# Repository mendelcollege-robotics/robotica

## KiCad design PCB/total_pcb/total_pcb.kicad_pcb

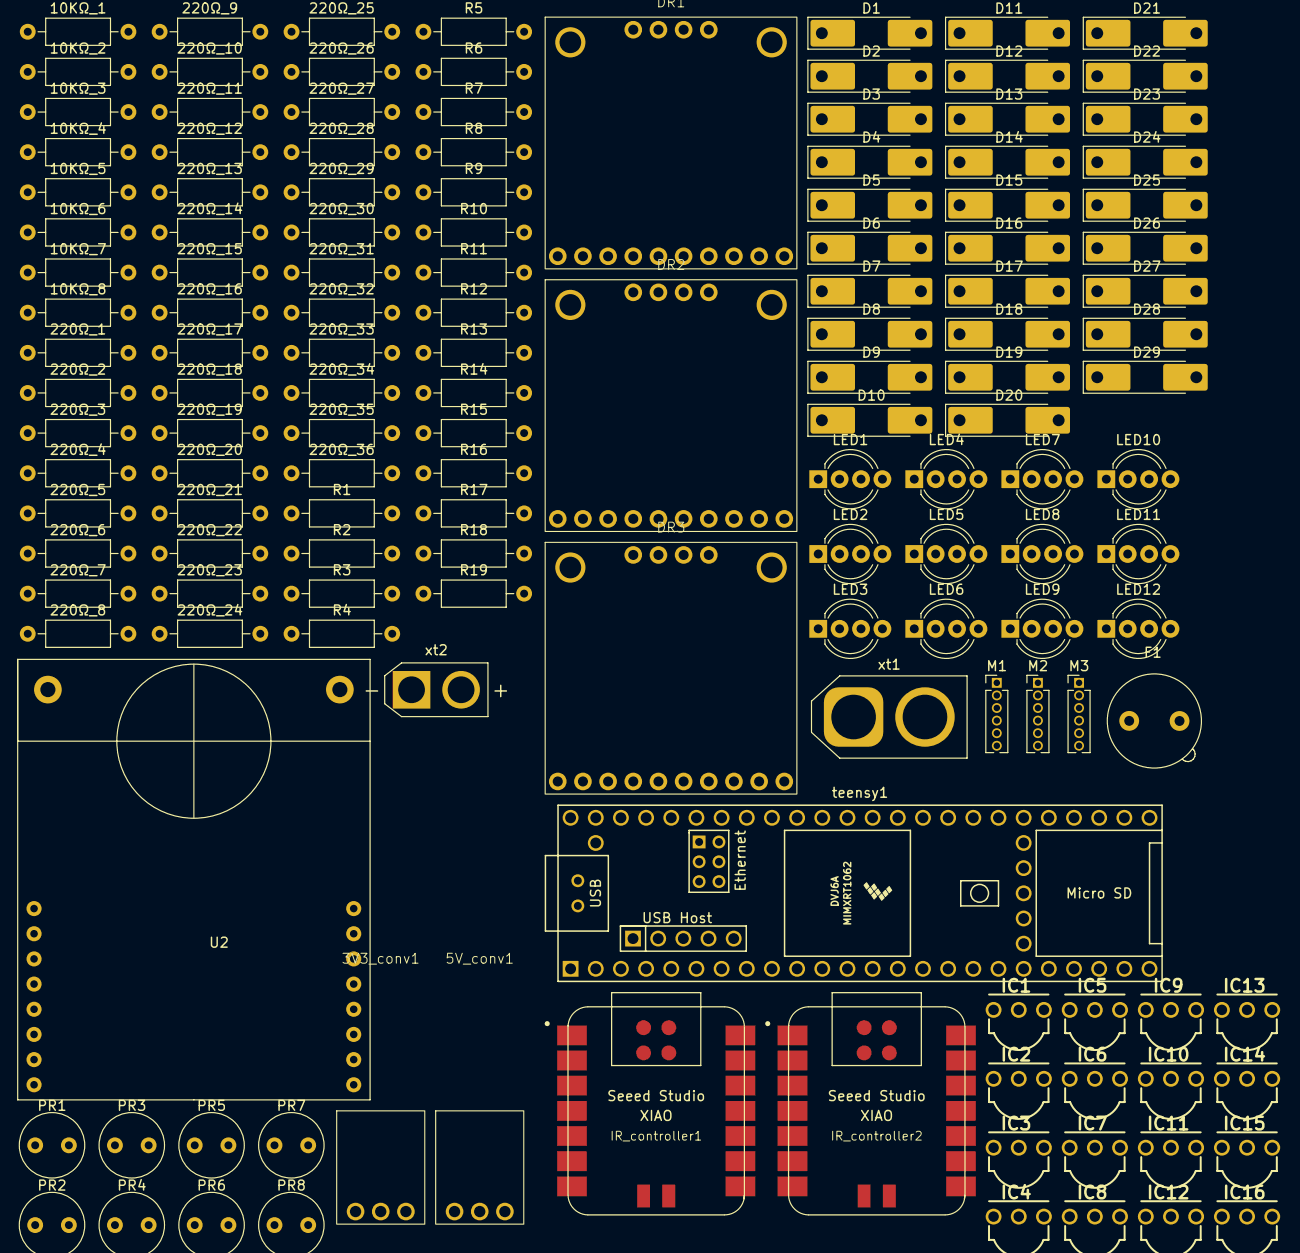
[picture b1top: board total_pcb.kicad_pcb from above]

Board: 2 copper layers, 143 parts (0 on the bottom side), 140 nets, no tracks yet.

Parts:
3V3_conv1, 5V_conv1: pololu-U1V10F5
10KΩ_1, 10KΩ_2, 10KΩ_3, 10KΩ_4, 10KΩ_5, 10KΩ_6, 10KΩ_7, 10KΩ_8, 220Ω_1, 220Ω_2, 220Ω_3, 220Ω_4, 220Ω_5, 220Ω_6, 220Ω_7, 220Ω_8, 220Ω_9, 220Ω_10, 220Ω_11, 220Ω_12, 220Ω_13, 220Ω_14, 220Ω_15, 220Ω_16, 220Ω_17, 220Ω_18, 220Ω_19, 220Ω_20, 220Ω_21, 220Ω_22, 220Ω_23, 220Ω_24, 220Ω_25, 220Ω_26, 220Ω_27, 220Ω_28, 220Ω_29, 220Ω_30, 220Ω_31, 220Ω_32, 220Ω_33, 220Ω_34, 220Ω_35, 220Ω_36: R_US; R_Axial_DIN0207_L6.3mm_D2.5mm_P10.16mm_Horizontal
D1, D2, D3, D4, D5, D6, D7, D8, D9, D10, D11, D12, D13, D14, D15, D16, D17, D18, D19, D20, D21, D22, D23, D24, D25, D26, D27, D28, D29: D; D_MELF-RM10_Universal_Handsoldering
DR1, DR2, DR3: TB9051FTG
F1: Fuse; Fuseholder_TR5_Littelfuse_No560_No460
IC1, IC2, IC3, IC4, IC5, IC6, IC7, IC8, IC9, IC10, IC11, IC12, IC13, IC14, IC15, IC16: TSSP4038
IR_controller1, IR_controller2: Seeed Studio XIAO SAMD21; XIAO-SAMD21-RP2040-14P-2.54-21X17.8MM (Seeeduino XIAO)
LED1, LED2, LED3, LED4, LED5, LED6, LED7, LED8, LED9, LED10, LED11, LED12: LED_KRGB; LED_D5.0mm-4_RGB_Wide_Pins
M1, M2, M3: PinHeader_1x06_P1.27mm_Vertical
PR1, PR2, PR3, PR4, PR5, PR6, PR7, PR8: A1050; R_LDR_D6.4mm_P3.4mm_Vertical
R1, R2, R3, R4, R5, R6, R7, R8, R9, R10, R11, R12, R13, R14, R15, R16, R17, R18, R19: R_US; R_Axial_DIN0207_L6.3mm_D2.5mm_P10.16mm_Horizontal
U2: openMV_M7_R2; openmv_m7_r2
teensy1: Teensy4.1; Teensy41
xt1: Battery; AMASS_XT60-F_1x02_P7.20mm_Vertical
xt2: Battery; AMASS_XT30U-M_1x02_P5.0mm_Vertical

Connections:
3v3: D7.2 (A), D21.1 (K)
5V: D16.2 (A), D23.1 (K)
5v: D8.2 (A), D20.1 (K)
BLAUW: R17.2, teensy1.38 (16_A2_RX4_SCL1)
GND: D17.1 (K), D24.2 (A), D26.2 (A)
GROEN: R18.2, teensy1.25 (33_MCLK2)
unnamed: 3V3_conv1.3 (VIN), 5V_conv1.3 (VIN), D12.1 (K)
unnamed: D1.2 (A), D4.2 (A), D7.1 (K)
unnamed: D1.1 (K), IR_controller1.12 (3V3)
unnamed: D2.2 (A), IR_controller1.13 (GND)
unnamed: D2.1 (K), D3.1 (K), D5.1 (K), D9.2 (A), D29.1 (K), U2.screw
unnamed: D3.2 (A), IR_controller2.13 (GND)
unnamed: D4.1 (K), IR_controller2.12 (3V3)
unnamed: D5.2 (A), U2.17 (gnd)
unnamed: D6.1 (K), U2.16 (vin)
unnamed: D10.2 (A), xt1.2 (-), xt2.2 (-)
unnamed: D10.1 (K), F1.2
unnamed: D11.2 (A), D13.1 (K), D26.1 (K), D27.2 (A), DR1.0 (screw), DR1.6 (GND), DR2.0 (screw), DR2.6 (GND), DR3.0 (screw), DR3.6 (GND)
unnamed: D11.1 (K), xt1.1 (+), xt2.1 (+)
unnamed: D12.2 (A), D25.2 (A), DR1.1 (VIN), DR2.1 (VIN), DR3.1 (VIN), F1.1
unnamed: D13.2 (A), D19.1 (K), D22.1 (K), D24.1 (K)
unnamed: D14.1 (K), D18.2 (A), D20.2 (A), D23.2 (A), DR1.7 (VCC), DR2.7 (VCC), DR3.7 (VCC), M1.4 (Vcc), M2.4 (Vcc), M3.4 (Vcc)
unnamed: D15.1 (K), D21.2 (A)
unnamed: D16.1 (K), PR1.1, PR2.1, PR3.1, PR4.1, PR5.1, PR6.1, PR7.1, PR8.1
unnamed: 10KΩ_1.2, 10KΩ_2.2, 10KΩ_3.2, 10KΩ_4.2, 10KΩ_5.2, 10KΩ_6.2, 10KΩ_7.2, 10KΩ_8.2, D17.2 (A), LED1.1 (K), LED2.1 (K), LED3.1 (K), LED4.1 (K), LED5.1 (K), LED6.1 (K), LED7.1 (K), LED8.1 (K), LED9.1 (K), LED10.1 (K), LED11.1 (K), LED12.1 (K)
unnamed: D18.1 (K), teensy1.48 (VIN)
unnamed: D19.2 (A), teensy1.47 (GND)
unnamed: D27.1 (K), DR1.2 (GND), DR2.2 (GND), DR3.2 (GND), M1.3 (GND), M2.3 (GND), M3.3 (GND)
unnamed: D6.2 (A), D8.1 (K), D28.2 (A)
unnamed: D28.1 (K), R1.2, R2.2, R3.2, R4.2, R5.2, R6.2, R7.2, R8.2, R9.2, R10.2, R11.2, R12.2, R13.2, R14.2, R15.2, R16.2
unnamed: D29.2 (A), IC1.2 (GND), IC2.2 (GND), IC3.2 (GND), IC4.2 (GND), IC5.2 (GND), IC6.2 (GND), IC7.2 (GND), IC8.2 (GND), IC9.2 (GND), IC10.2 (GND), IC11.2 (GND), IC12.2 (GND), IC13.2 (GND), IC14.2 (GND), IC15.2 (GND), IC16.2 (GND)
unnamed: DR1.9 (EN), teensy1.19 (27_A13_SCK1)
unnamed: DR1.10 (ENB), teensy1.18 (26_A12_MOSI1)
unnamed: DR1.4 (OUT1), M1.1 (MotorPW)
unnamed: DR1.3 (OUT2), M1.2 (MotorPW)
unnamed: DR1.12 (PWM1), teensy1.16 (24_A10_TX6_SCL2)
unnamed: DR1.11 (PWM2), teensy1.17 (25_A11_RX6_SDA2)
unnamed: DR2.9 (EN), teensy1.14 (12_MISO_MQSL)
unnamed: DR2.10 (ENB), teensy1.13 (11_MOSI_CTX1)
unnamed: DR2.4 (OUT1), M2.1 (MotorPW)
unnamed: DR2.3 (OUT2), M2.2 (MotorPW)
unnamed: DR2.12 (PWM1), teensy1.11 (9_OUT1C)
unnamed: DR2.11 (PWM2), teensy1.12 (10_CS_MQSR)
unnamed: DR3.9 (EN), teensy1.8 (6_OUT1D)
unnamed: DR3.10 (ENB), teensy1.7 (5_IN2)
unnamed: DR3.4 (OUT1), M3.1 (MotorPW)
unnamed: DR3.3 (OUT2), M3.2 (MotorPW)
unnamed: DR3.12 (PWM1), teensy1.5 (3_LRCLK2)
unnamed: DR3.11 (PWM2), teensy1.6 (4_BCLK2)
unnamed: IC1.1 (OUT), IR_controller1.1 (PA02_A0_D0)
unnamed: IC1.3 (VS), R1.1
unnamed: IC2.1 (OUT), IR_controller1.2 (PA4_A1_D1)
unnamed: IC2.3 (VS), R2.1
unnamed: IC3.3 (VS), R3.1
unnamed: IC4.1 (OUT), IR_controller1.3 (PA10_A2_D2)
unnamed: IC4.3 (VS), R4.1
unnamed: IC5.1 (OUT), IR_controller1.4 (PA11_A3_D3)
unnamed: IC5.3 (VS), R5.1
unnamed: IC6.1 (OUT), IR_controller1.5 (PA8_A4_D4_SDA)
unnamed: IC6.3 (VS), R6.1
unnamed: IC7.1 (OUT), IR_controller1.6 (PA9_A5_D5_SCL)
unnamed: IC7.3 (VS), R7.1
unnamed: IC8.1 (OUT), IR_controller1.9 (PA7_A8_D8_SCK)
unnamed: IC8.3 (VS), R8.1
unnamed: IC9.1 (OUT), IR_controller2.1 (PA02_A0_D0)
unnamed: IC9.3 (VS), R9.1
unnamed: IC10.1 (OUT), IR_controller2.2 (PA4_A1_D1)
unnamed: IC10.3 (VS), R10.1
unnamed: IC11.3 (VS), R11.1
unnamed: IC12.1 (OUT), IR_controller2.3 (PA10_A2_D2)
unnamed: IC12.3 (VS), R12.1
unnamed: IC13.1 (OUT), IR_controller2.4 (PA11_A3_D3)
unnamed: IC13.3 (VS), R13.1
unnamed: IC14.1 (OUT), IR_controller2.5 (PA8_A4_D4_SDA)
unnamed: IC14.3 (VS), R14.1
unnamed: IC15.1 (OUT), IR_controller2.6 (PA9_A5_D5_SCL)
unnamed: IC15.3 (VS), R15.1
unnamed: IC16.1 (OUT), IR_controller2.9 (PA7_A8_D8_SCK)
unnamed: IC16.3 (VS), R16.1
unnamed: 220Ω_3.1, LED1.4 (BA)
unnamed: 220Ω_2.1, LED1.3 (GA)
unnamed: 220Ω_1.1, LED1.2 (RA)
unnamed: 220Ω_6.1, LED2.4 (BA)
unnamed: 220Ω_5.1, LED2.3 (GA)
unnamed: 220Ω_4.1, LED2.2 (RA)
unnamed: 220Ω_9.1, LED3.4 (BA)
unnamed: 220Ω_8.1, LED3.3 (GA)
unnamed: 220Ω_7.1, LED3.2 (RA)
unnamed: 220Ω_12.1, LED4.4 (BA)
unnamed: 220Ω_11.1, LED4.3 (GA)
unnamed: 220Ω_10.1, LED4.2 (RA)
unnamed: 220Ω_15.1, LED5.4 (BA)
unnamed: 220Ω_14.1, LED5.3 (GA)
unnamed: 220Ω_13.1, LED5.2 (RA)
unnamed: 220Ω_18.1, LED6.4 (BA)
unnamed: 220Ω_17.1, LED6.3 (GA)
unnamed: 220Ω_16.1, LED6.2 (RA)
unnamed: 220Ω_21.1, LED7.4 (BA)
unnamed: 220Ω_20.1, LED7.3 (GA)
unnamed: 220Ω_19.1, LED7.2 (RA)
unnamed: 220Ω_24.1, LED8.4 (BA)
unnamed: 220Ω_23.1, LED8.3 (GA)
unnamed: 220Ω_22.1, LED8.2 (RA)
unnamed: 220Ω_27.1, LED9.4 (BA)
unnamed: 220Ω_26.1, LED9.3 (GA)
unnamed: 220Ω_25.1, LED9.2 (RA)
unnamed: 220Ω_30.1, LED10.4 (BA)
unnamed: 220Ω_29.1, LED10.3 (GA)
unnamed: 220Ω_28.1, LED10.2 (RA)
unnamed: 220Ω_33.1, LED11.4 (BA)
unnamed: 220Ω_32.1, LED11.3 (GA)
unnamed: 220Ω_31.1, LED11.2 (RA)
unnamed: 220Ω_36.1, LED12.4 (BA)
unnamed: 220Ω_35.1, LED12.3 (GA)
unnamed: 220Ω_34.1, LED12.2 (RA)
unnamed: M1.5 (A_out), teensy1.20 (28_RX7)
unnamed: M1.6 (B_out), teensy1.45 (23_A9_CRX1_MCLK1)
unnamed: M2.5 (A_out), teensy1.22 (30_CRX3)
unnamed: M2.6 (B_out), teensy1.21 (29_TX7)
unnamed: M3.5 (A_out), teensy1.24 (32_OUT1B)
unnamed: M3.6 (B_out), teensy1.23 (31_CTX3)
unnamed: 220Ω_3.2, 220Ω_6.2, 220Ω_9.2, 220Ω_12.2, 220Ω_15.2, 220Ω_18.2, 220Ω_21.2, 220Ω_24.2, 220Ω_27.2, 220Ω_30.2, 220Ω_33.2, 220Ω_36.2
unnamed: 220Ω_2.2, 220Ω_5.2, 220Ω_8.2, 220Ω_11.2, 220Ω_14.2, 220Ω_17.2, 220Ω_20.2, 220Ω_23.2, 220Ω_26.2, 220Ω_29.2, 220Ω_32.2, 220Ω_35.2
unnamed: 220Ω_1.2, 220Ω_4.2, 220Ω_7.2, 220Ω_10.2, 220Ω_13.2, 220Ω_16.2, 220Ω_19.2, 220Ω_22.2, 220Ω_25.2, 220Ω_28.2, 220Ω_31.2, 220Ω_34.2
ROOD: R19.2, teensy1.26 (34_RX8)
gnd: D9.1 (K), D22.2 (A)
pr1: 10KΩ_1.1, PR1.2, teensy1.35 (13_SCK_LED)
pr2: 10KΩ_2.1, PR2.2, teensy1.33 (41_A17)
pr3: 10KΩ_3.1, PR3.2, teensy1.32 (40_A16)
pr4: 10KΩ_4.1, PR4.2, teensy1.31 (39_MISO1_OUT1A)
pr5: 10KΩ_5.1, PR5.2, teensy1.30 (38_CS1_IN1)
pr6: 10KΩ_6.1, PR6.2, teensy1.29 (37_CS)
pr7: 10KΩ_7.1, PR7.2, teensy1.28 (36_CS)
pr8: 10KΩ_8.1, PR8.2, teensy1.27 (35_TX8)
rx1: U2.3 (p1/TX/miso), teensy1.2 (0_RX1_CRX2_CS1)
rx2: IR_controller1.7 (PB08_A6_D6_TX), teensy1.9 (7_RX2_OUT1A)
rx3: IR_controller2.7 (PB08_A6_D6_TX), teensy1.37 (15_A1_RX3_SPDIF_IN)
tx1: U2.2 (p0/RX/mosi), teensy1.3 (1_TX1_CTX2_MISO1)
tx2: IR_controller1.8 (PB09_A7_D7_RX), teensy1.10 (8_TX2_IN1)
tx3: IR_controller2.8 (PB09_A7_D7_RX), teensy1.36 (14_A0_TX3_SPDIF_OUT)

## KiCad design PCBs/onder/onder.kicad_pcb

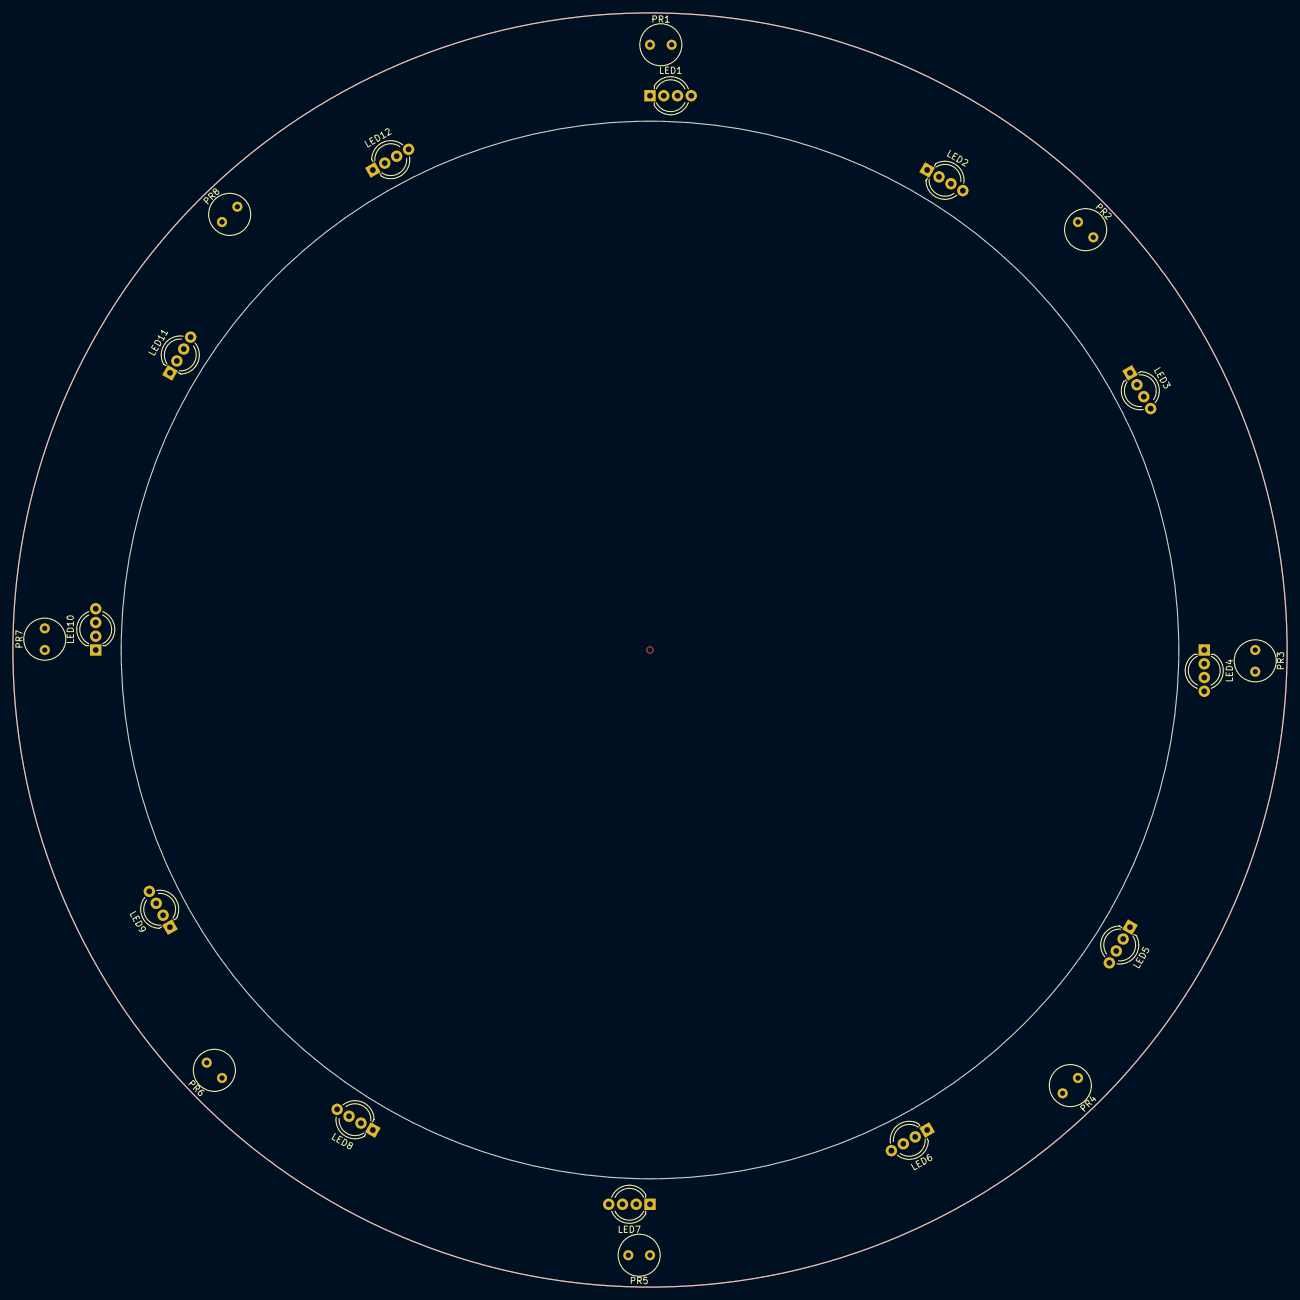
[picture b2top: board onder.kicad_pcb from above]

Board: 2 copper layers, 200.0 x 200.0 mm, 20 parts (0 on the bottom side), 2 nets, no tracks yet.

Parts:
LED1, LED2, LED3, LED4, LED5, LED6, LED7, LED8, LED9, LED10, LED11, LED12: LED_KRGB; LED_D5.0mm-4_RGB_Wide_Pins
PR1, PR2, PR3, PR4, PR5, PR6, PR7, PR8: A1050; R_LDR_D6.4mm_P3.4mm_Vertical

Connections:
5V: PR1.1, PR2.1, PR3.1, PR4.1, PR5.1, PR6.1, PR7.1, PR8.1
GND: LED1.1 (K), LED2.1 (K), LED3.1 (K), LED4.1 (K), LED5.1 (K), LED6.1 (K), LED7.1 (K), LED8.1 (K), LED9.1 (K), LED10.1 (K), LED11.1 (K), LED12.1 (K)

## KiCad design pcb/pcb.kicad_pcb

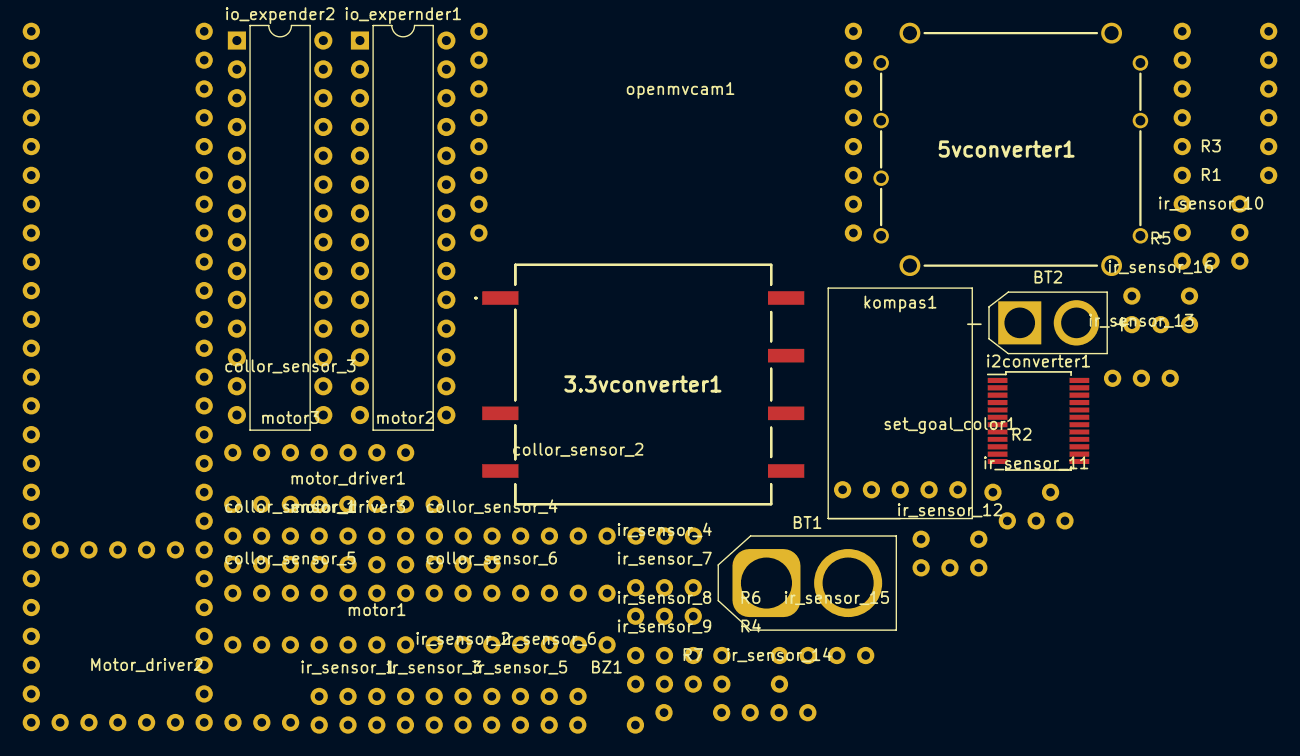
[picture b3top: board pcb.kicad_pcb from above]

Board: 2 copper layers, 48 parts (0 on the bottom side), 66 nets, no tracks yet.

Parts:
3.3vconverter1: CC6-1203SR-E; CC60512SRE
5vconverter1: CC6-1205SF-E; CC6_SF
BT1: Battery; AMASS_XT60-F_1x02_P7.20mm_Vertical
BT2: Battery; AMASS_XT30U-F_1x02_P5.0mm_Vertical
BZ1: Buzzer; buzer
Motor_driver2: TB9051FTG
R1, R2, R3, R4, R5, R6, R7: R; resistor
collor_sensor_1, collor_sensor_2, collor_sensor_3, collor_sensor_4, collor_sensor_5, collor_sensor_6: tcs3472_color_sensor; tcs3472
controllboard1: Teensy4.1; teensy4.1
i2converter1: PCA9548ADB; SSOP-24_5.3x8.2mm_P0.65mm
io_expender2: MCP23017_SP; DIP-28_W7.62mm
io_expernder1: MCP23017_SP; DIP-28_W7.62mm
ir_sensor_1, ir_sensor_2, ir_sensor_3, ir_sensor_4, ir_sensor_5, ir_sensor_6, ir_sensor_7, ir_sensor_8, ir_sensor_9, ir_sensor_10, ir_sensor_11, ir_sensor_12, ir_sensor_13, ir_sensor_14, ir_sensor_15, ir_sensor_16: tssp4038
kompas1: miniIMU-9_v6
motor1, motor2, motor3: pololu_motor
motor_driver1, motor_driver3: TB9051FTG
openmvcam1: openMV_M7_R2; openmv_m7_r2
set_goal_color1: SW_DIP_x01; dipswitch1
settings1: SW_DIP_x06; dipswitch6

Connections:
12v: 3.3vconverter1.1, 5vconverter1.1, BT1.2, BT2.2
unnamed: 3.3vconverter1.5, R1.2, collor_sensor_1.3, collor_sensor_2.3, collor_sensor_3.3, collor_sensor_4.3, collor_sensor_5.3, collor_sensor_6.3, i2converter1.12, io_expender2.10, io_expernder1.10, ir_sensor_1.2, ir_sensor_2.2, ir_sensor_3.2, ir_sensor_4.2, ir_sensor_5.2, ir_sensor_6.2, ir_sensor_7.2, ir_sensor_8.2, ir_sensor_9.2, ir_sensor_10.2, ir_sensor_11.2, ir_sensor_12.2, ir_sensor_13.2, ir_sensor_14.2, ir_sensor_15.2, ir_sensor_16.2
unnamed: 3.3vconverter1.7, collor_sensor_1.2, collor_sensor_2.2, collor_sensor_3.2, collor_sensor_4.2, collor_sensor_5.2, collor_sensor_6.2, i2converter1.24, io_expender2.9, io_expernder1.9, ir_sensor_1.1, ir_sensor_2.1, ir_sensor_3.1, ir_sensor_4.1, ir_sensor_5.1, ir_sensor_6.1, ir_sensor_7.1, ir_sensor_8.1, ir_sensor_9.1, ir_sensor_10.1, ir_sensor_11.1, ir_sensor_12.1, ir_sensor_13.1, ir_sensor_14.1, ir_sensor_15.1, ir_sensor_16.1, set_goal_color1.1
unnamed: 5vconverter1.5, BZ1.2, Motor_driver2.6, R2.2, R3.2, R4.2, R5.2, R6.2, R7.2, controllboard1.47, kompas1.2, motor1.4, motor2.4, motor3.4, motor_driver1.6, motor_driver3.6
unnamed: 5vconverter1.7, Motor_driver2.7, controllboard1.48, kompas1.3, motor1.1, motor2.1, motor3.1, motor_driver1.7, motor_driver3.7
unnamed: BZ1.1, controllboard1.10
unnamed: Motor_driver2.9, io_expender2.5
unnamed: Motor_driver2.10, io_expender2.4
unnamed: Motor_driver2.11, io_expender2.3
unnamed: Motor_driver2.12, io_expender2.2
unnamed: R1.1, set_goal_color1.2
unnamed: R2.1, controllboard1.4, settings1.7
unnamed: R3.1, controllboard1.5, settings1.8
unnamed: R4.1, controllboard1.6, settings1.9
unnamed: R5.1, controllboard1.7, settings1.10
unnamed: R6.1, controllboard1.8, settings1.11
unnamed: R7.1, controllboard1.9, settings1.12
unnamed: collor_sensor_1.0, i2converter1.15
unnamed: collor_sensor_1.1, i2converter1.16
unnamed: collor_sensor_2.0, i2converter1.13
unnamed: collor_sensor_2.1, i2converter1.14
unnamed: collor_sensor_3.0, i2converter1.10
unnamed: collor_sensor_3.1, i2converter1.11
unnamed: collor_sensor_4.0, i2converter1.9
unnamed: collor_sensor_4.1, i2converter1.8
unnamed: collor_sensor_5.0, i2converter1.6
unnamed: collor_sensor_5.1, i2converter1.7
unnamed: collor_sensor_6.0, i2converter1.4
unnamed: collor_sensor_6.1, i2converter1.5
unnamed: controllboard1.40, i2converter1.23, kompas1.1
unnamed: controllboard1.41, i2converter1.22, kompas1.0
unnamed: controllboard1.44, motor_driver3.11
unnamed: controllboard1.46, settings1.1, settings1.2, settings1.3, settings1.4, settings1.5, settings1.6
unnamed: i2converter1.17, io_expernder1.13
unnamed: i2converter1.18, io_expernder1.12
unnamed: i2converter1.19, io_expender2.13
unnamed: i2converter1.20, io_expender2.12
unnamed: io_expender2.1, motor_driver3.9
unnamed: io_expender2.6, motor_driver1.12
unnamed: io_expender2.7, motor_driver1.11
unnamed: io_expender2.8, motor_driver1.10
unnamed: io_expender2.21, motor_driver1.9
unnamed: io_expender2.22, ir_sensor_15.3
unnamed: io_expender2.23, ir_sensor_14.3
unnamed: io_expender2.24, motor_driver3.10
unnamed: io_expender2.25, motor2.2
unnamed: io_expender2.26, motor2.3
unnamed: io_expender2.27, motor3.2
unnamed: io_expender2.28, motor3.3
unnamed: io_expernder1.1, ir_sensor_1.3
unnamed: io_expernder1.2, ir_sensor_2.3
unnamed: io_expernder1.3, ir_sensor_4.3
unnamed: io_expernder1.4, ir_sensor_5.3
unnamed: io_expernder1.5, ir_sensor_6.3
unnamed: io_expernder1.6, ir_sensor_7.3
unnamed: io_expernder1.7, ir_sensor_8.3
unnamed: io_expernder1.8, ir_sensor_9.3
unnamed: io_expernder1.21, ir_sensor_10.3
unnamed: io_expernder1.22, ir_sensor_11.3
unnamed: io_expernder1.23, ir_sensor_12.3
unnamed: io_expernder1.24, ir_sensor_13.3
unnamed: io_expernder1.25, ir_sensor_16.3
unnamed: io_expernder1.26, ir_sensor_3.3
unnamed: io_expernder1.27, motor1.2
unnamed: io_expernder1.28, motor1.3
gnd: 3.3vconverter1.3, 5vconverter1.3, BT1.1, BT2.1

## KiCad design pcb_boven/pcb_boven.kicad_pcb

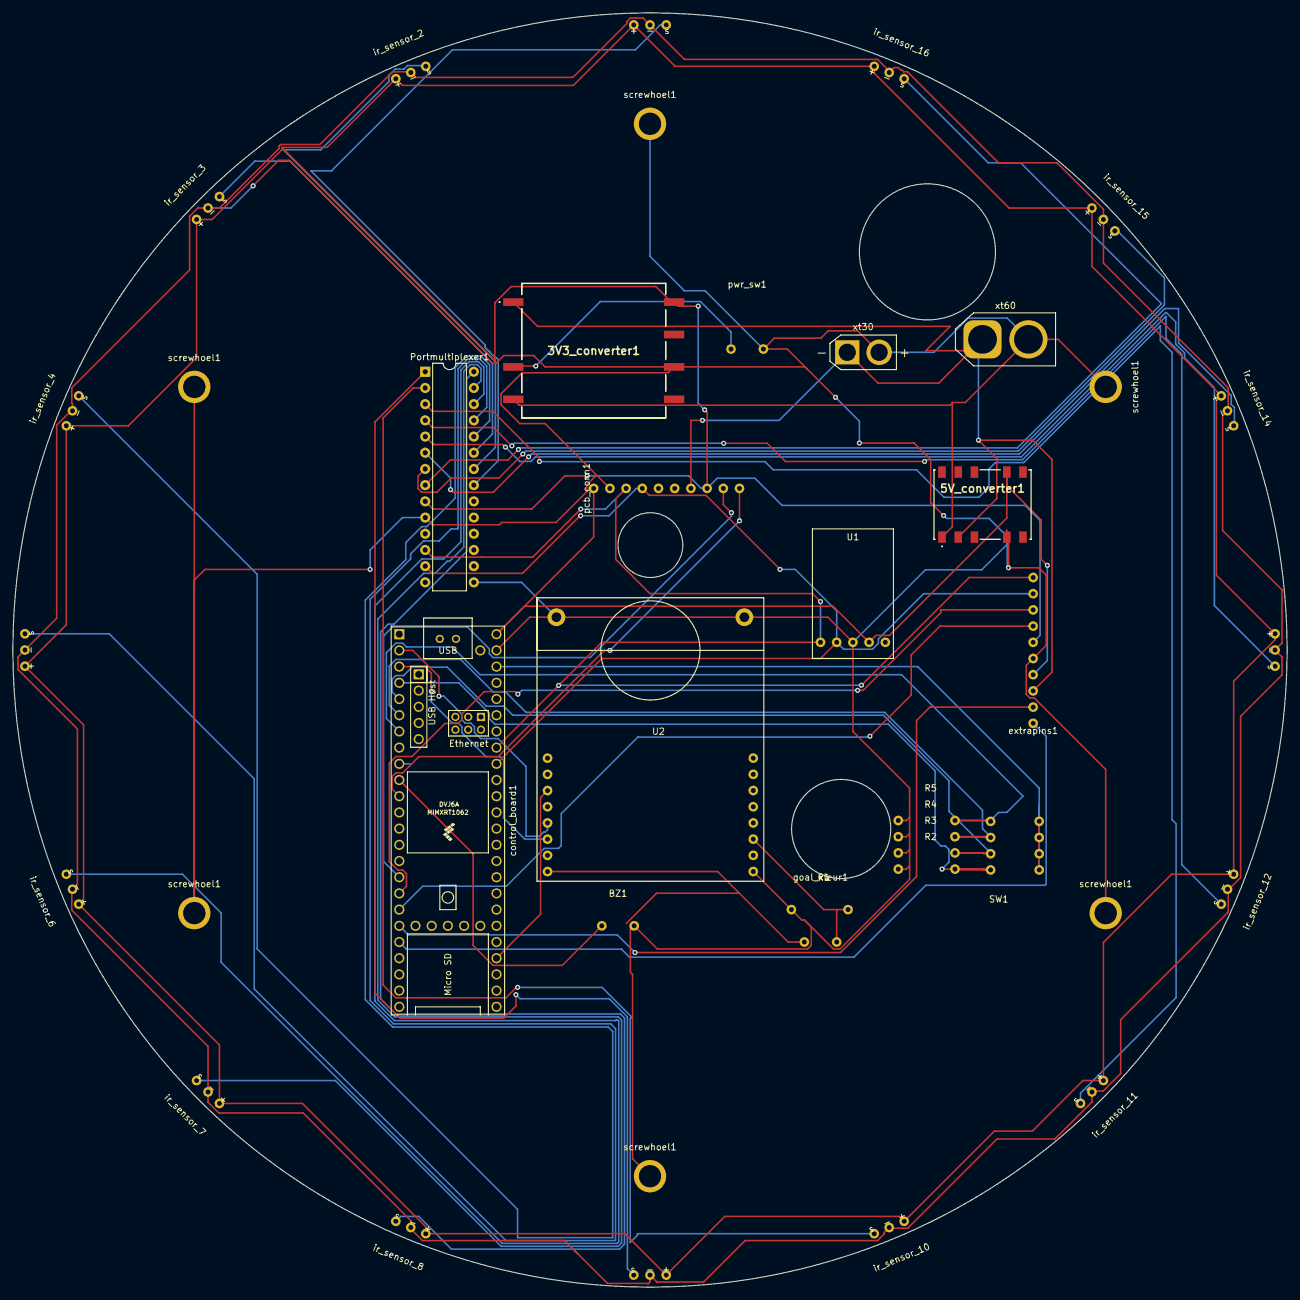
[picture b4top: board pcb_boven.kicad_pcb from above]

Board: 2 copper layers, 199.8 x 199.8 mm, 41 parts (0 on the bottom side), 38 nets.

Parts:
3V3_converter1: CC6-1203SR-E; CC60512SRE
5V_converter1: SFTN01M-05N; SFTN01M05N
BZ1: Buzzer; buzer
Portmultiplexer1: MCP23017_SP; DIP-28_W7.62mm
R1, R2, R3, R4, R5: R; resistor
SW1: SW_DIP_x04; dipswitch4
U1: miniIMU-9_v6
U2: openMV_M7_R2; openmv_m7_r2
control_board1: Teensy4.1; Teensy41
extrapins1: Conn_01x10_Female; 10connect
goal_kleur1: SW_DIP_x01; dipswitch1
ir_sensor_1, ir_sensor_2, ir_sensor_3, ir_sensor_4, ir_sensor_5, ir_sensor_6, ir_sensor_7, ir_sensor_8, ir_sensor_9, ir_sensor_10, ir_sensor_11, ir_sensor_12, ir_sensor_13, ir_sensor_14, ir_sensor_15, ir_sensor_16: tssp4038
pcb_conn1: Conn_01x10_Female; 10connect
pwr_sw1: SW_DIP_x01; dipswitch1
screwhoel1, screwhoel1#2, screwhoel1#3, screwhoel1#4, screwhoel1#5, screwhoel1#6: screw_hole; screwhole
xt30: Battery; AMASS_XT30U-F_1x02_P5.0mm_Vertical
xt60: Battery; AMASS_XT60-F_1x02_P7.20mm_Vertical

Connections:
3.3v: 3V3_converter1.7, Portmultiplexer1.9, U2.9, extrapins1.6, goal_kleur1.1, ir_sensor_1.1, ir_sensor_2.1, ir_sensor_3.1, ir_sensor_4.1, ir_sensor_5.1, ir_sensor_6.1, ir_sensor_7.1, ir_sensor_8.1, ir_sensor_9.1, ir_sensor_10.1, ir_sensor_11.1, ir_sensor_12.1, ir_sensor_13.1, ir_sensor_14.1, ir_sensor_15.1, ir_sensor_16.1, pcb_conn1.8
5v: 5V_converter1.8, U1.3, control_board1.48, extrapins1.4, pcb_conn1.1
12V: 3V3_converter1.1, 5V_converter1.2, extrapins1.3, pcb_conn1.7, xt30.1, xt60.1
25: control_board1.17, extrapins1.8
26: control_board1.18, extrapins1.7
27: control_board1.19, extrapins1.2
28: control_board1.20, extrapins1.1
A: control_board1.16, pcb_conn1.9
B: control_board1.11, pcb_conn1.10
unnamed: 3V3_converter1.2, pwr_sw1.1
unnamed: BZ1.1, control_board1.10
unnamed: Portmultiplexer1.1, ir_sensor_9.3
unnamed: Portmultiplexer1.2, ir_sensor_10.3
unnamed: Portmultiplexer1.3, ir_sensor_11.3
unnamed: Portmultiplexer1.4, ir_sensor_12.3
unnamed: Portmultiplexer1.5, ir_sensor_13.3
unnamed: Portmultiplexer1.6, ir_sensor_14.3
unnamed: Portmultiplexer1.7, ir_sensor_15.3
unnamed: Portmultiplexer1.8, ir_sensor_16.3
unnamed: Portmultiplexer1.21, ir_sensor_1.3
unnamed: Portmultiplexer1.22, ir_sensor_2.3
unnamed: Portmultiplexer1.23, ir_sensor_3.3
unnamed: Portmultiplexer1.24, ir_sensor_4.3
unnamed: Portmultiplexer1.25, ir_sensor_5.3
unnamed: Portmultiplexer1.26, ir_sensor_6.3
unnamed: Portmultiplexer1.27, ir_sensor_7.3
unnamed: Portmultiplexer1.28, ir_sensor_8.3
unnamed: R1.2, U2.15, goal_kleur1.2
unnamed: R2.2, SW1.8, control_board1.4
unnamed: R3.2, SW1.7, control_board1.5
unnamed: R4.2, SW1.6, control_board1.6
unnamed: R5.2, SW1.5, control_board1.7
unnamed: SW1.1, SW1.2, SW1.3, SW1.4, control_board1.46
unnamed: U2.6, control_board1.2
unnamed: U2.7, control_board1.3
gnd: 3V3_converter1.3, 3V3_converter1.5, 5V_converter1.1, 5V_converter1.5, BZ1.2, Portmultiplexer1.10, Portmultiplexer1.15, Portmultiplexer1.16, Portmultiplexer1.17, R1.1, R2.1, R3.1, R4.1, R5.1, U1.2, U2.17, U2.screw, control_board1.47, extrapins1.5, ir_sensor_1.2, ir_sensor_2.2, ir_sensor_3.2, ir_sensor_4.2, ir_sensor_5.2, ir_sensor_6.2, ir_sensor_7.2, ir_sensor_8.2, ir_sensor_9.2, ir_sensor_10.2, ir_sensor_11.2, ir_sensor_12.2, ir_sensor_13.2, ir_sensor_14.2, ir_sensor_15.2, ir_sensor_16.2, pcb_conn1.2, pwr_sw1.2, screwhoel1.1, screwhoel1#2.1, screwhoel1#3.1, screwhoel1#4.1, screwhoel1#5.1, screwhoel1#6.1, xt30.2, xt60.2
scl: Portmultiplexer1.12, U1.0, control_board1.41, extrapins1.10, pcb_conn1.3
sda: Portmultiplexer1.13, U1.1, control_board1.40, extrapins1.9, pcb_conn1.4

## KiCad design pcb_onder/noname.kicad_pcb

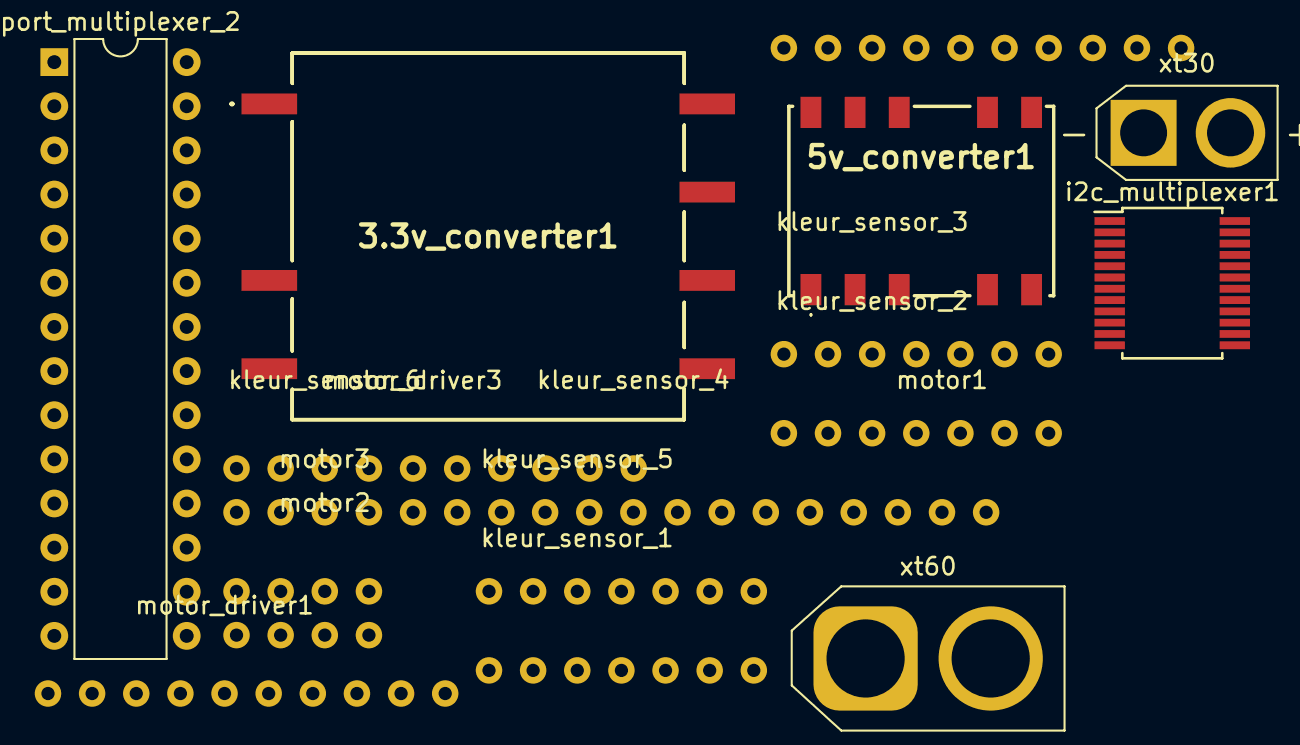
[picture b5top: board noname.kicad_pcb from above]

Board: 2 copper layers, 18 parts (0 on the bottom side), 32 nets, no tracks yet.

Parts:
3.3v_converter1: CC6-1203SR-E; CC60512SRE
5v_converter1: SFTN01M-05N; SFTN01M05N
i2c_multiplexer1: PCA9548ADB; SSOP-24_5.3x8.2mm_P0.65mm
kleur_sensor_1, kleur_sensor_2, kleur_sensor_3, kleur_sensor_4, kleur_sensor_5, kleur_sensor_6: tcs3472_color_sensor; tcs3472
motor1, motor2, motor3: pololu_motor
motor_driver1, motor_driver2, motor_driver3: TB9051FTG
port_multiplexer_2: MCP23017_SP; DIP-28_W7.62mm
xt30: Battery; AMASS_XT30U-F_1x02_P5.0mm_Vertical
xt60: Battery; AMASS_XT60-F_1x02_P7.20mm_Vertical

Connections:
3.3v: 3.3v_converter1.7, i2c_multiplexer1.24, kleur_sensor_1.2, kleur_sensor_2.2, kleur_sensor_3.2, kleur_sensor_4.2, kleur_sensor_5.2, kleur_sensor_6.2, motor_driver1.7, motor_driver2.7, motor_driver3.7, port_multiplexer_2.9
5v: 5v_converter1.8, motor1.1, motor2.1, motor3.1
+12v: 3.3v_converter1.1, 5v_converter1.2, xt30.2, xt60.2
unnamed: i2c_multiplexer1.4, kleur_sensor_1.0
unnamed: i2c_multiplexer1.5, kleur_sensor_1.1
unnamed: i2c_multiplexer1.6, kleur_sensor_2.0
unnamed: i2c_multiplexer1.7, kleur_sensor_2.1
unnamed: i2c_multiplexer1.8, kleur_sensor_3.0
unnamed: i2c_multiplexer1.9, kleur_sensor_3.1
unnamed: i2c_multiplexer1.10, kleur_sensor_4.0
unnamed: i2c_multiplexer1.11, kleur_sensor_4.1
unnamed: i2c_multiplexer1.13, kleur_sensor_5.0
unnamed: i2c_multiplexer1.14, kleur_sensor_5.1
unnamed: i2c_multiplexer1.15, kleur_sensor_6.0
unnamed: i2c_multiplexer1.16, kleur_sensor_6.1
unnamed: motor1.2, port_multiplexer_2.25
unnamed: motor1.3, port_multiplexer_2.26
unnamed: motor2.2, port_multiplexer_2.27
unnamed: motor2.3, port_multiplexer_2.28
unnamed: motor_driver1.9, port_multiplexer_2.4
unnamed: motor_driver1.10, port_multiplexer_2.3
unnamed: motor_driver1.11, port_multiplexer_2.2
unnamed: motor_driver1.12, port_multiplexer_2.1
unnamed: motor_driver2.9, port_multiplexer_2.8
unnamed: motor_driver2.10, port_multiplexer_2.7
unnamed: motor_driver2.11, port_multiplexer_2.6
unnamed: motor_driver2.12, port_multiplexer_2.5
unnamed: motor_driver3.9, port_multiplexer_2.24
unnamed: motor_driver3.10, port_multiplexer_2.23
unnamed: motor_driver3.11, port_multiplexer_2.22
unnamed: motor_driver3.12, port_multiplexer_2.21
gnd: 3.3v_converter1.3, 3.3v_converter1.5, 5v_converter1.1, 5v_converter1.5, i2c_multiplexer1.12, kleur_sensor_1.3, kleur_sensor_2.3, kleur_sensor_3.3, kleur_sensor_4.3, kleur_sensor_5.3, kleur_sensor_6.3, motor1.4, motor2.4, motor3.4, motor_driver1.6, motor_driver2.6, motor_driver3.6, port_multiplexer_2.10, xt30.1, xt60.1
